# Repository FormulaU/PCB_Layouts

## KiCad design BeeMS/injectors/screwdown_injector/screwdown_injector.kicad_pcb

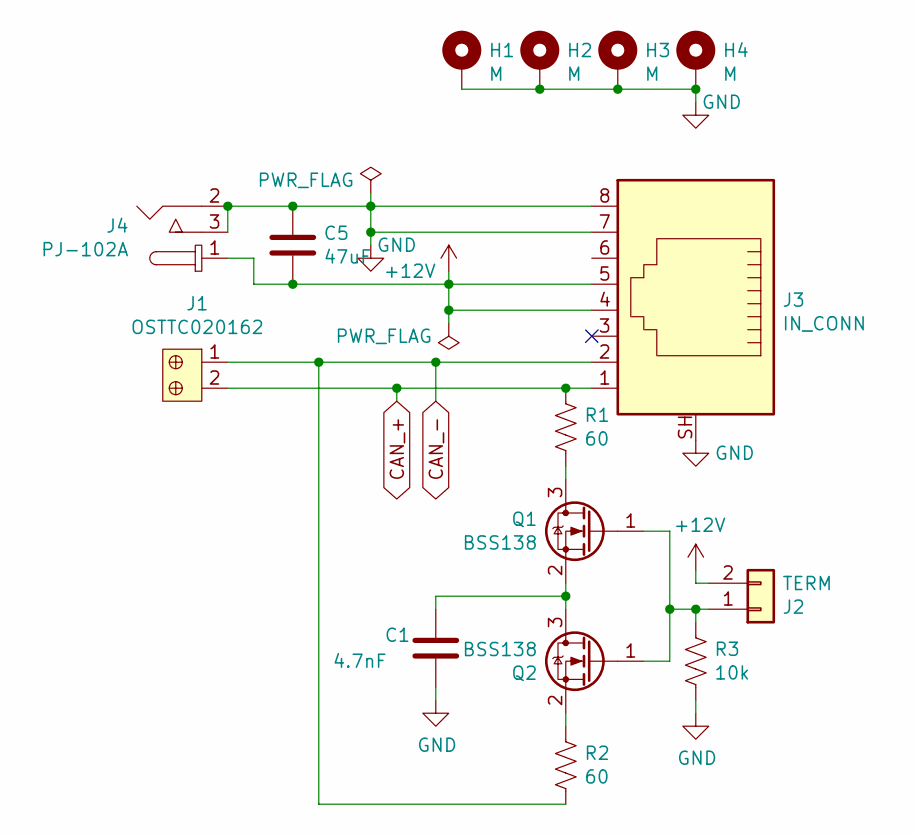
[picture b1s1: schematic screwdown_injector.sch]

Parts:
C1: 4.7nF; C_1206_3216Metric_Pad1.42x1.75mm_HandSolder; MPN 885012208079; Digi-Key_PN 732-8119-1-ND
C5: 47uF; C_1210_3225Metric_Pad1.42x2.65mm_HandSolder; MPN RM32EC81C476KE15L; Digi-Key_PN 490-10531-1-ND
H1, H2, H3, H4: M; MountingHole_2.2mm_M2_DIN965_Pad
J1: OSTTC020162; Term_Block_1x2_P5mm; MPN OSTTC020162; Digi-Key_PN ED2600-ND
J2: TERM; PinHeader_1x02_P2.54mm_Vertical
J3: IN_CONN; RJ45_Amphenol_RJHSE5380; MPN RJHSE-5380; Digi-Key_PN RJHSE-5380-ND
J4: PJ-102A; Barrel_Jack_5.5mmODx2.1mmID_PJ-102A; MPN PJ-102A; Digi-Key_PN CP-102A-ND
Q1, Q2: BSS138; SOT-23; MPN BSS138CT; Digi-Key_PN BSS138CT-ND
R1, R2: 60; R_2512_6332Metric_Pad1.52x3.35mm_HandSolder; MPN ERJ-P08J750V; Digi-Key_PN P75ALCT-ND
R3: 10k; R_1206_3216Metric; MPN RC1206JR-0710KL; Digi-Key_PN 311-10KERCT-ND

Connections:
+12V: C5.2, J2.2, J3.4, J3.5, J4.1
CAN_+: J1.2, J3.1, R1.1
CAN_-: J1.1, J3.2, R2.2
GND: C1.2, C5.1, H1.1, H2.1, H3.1, H4.1, J3.7, J3.8, J3.SH, J4.2, J4.3, R3.2
unnamed: C1.1, Q1.2 (S), Q2.3 (D)
unnamed: J2.1, Q1.1 (G), Q2.1 (G), R3.1
unnamed: Q1.3 (D), R1.2
unnamed: Q2.2 (S), R2.1

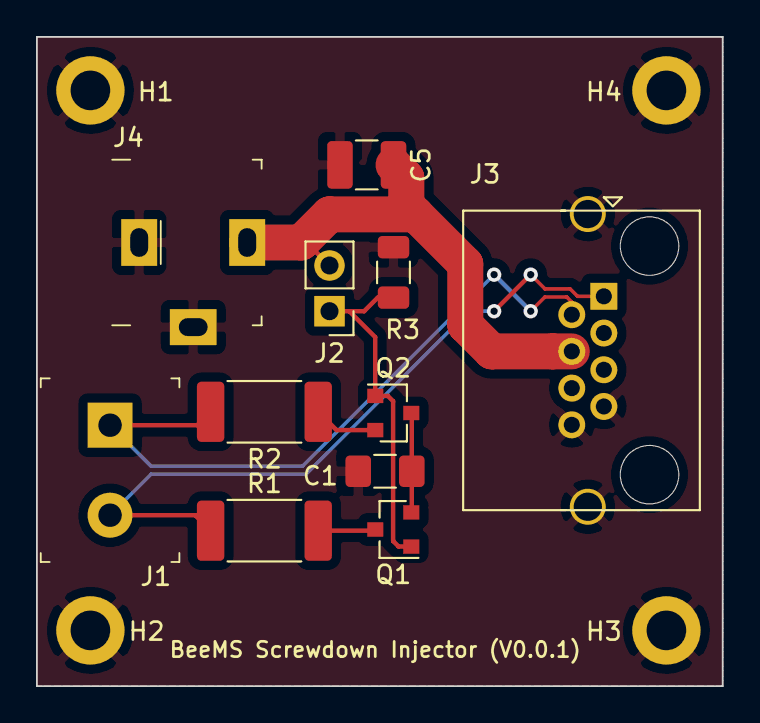
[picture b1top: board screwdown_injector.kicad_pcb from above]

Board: 2 copper layers, 38.1 x 36.1 mm, 16 parts (1 on the bottom side), 8 nets.

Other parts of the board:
svg2mod: G***; Half-U-Half-car-thresh

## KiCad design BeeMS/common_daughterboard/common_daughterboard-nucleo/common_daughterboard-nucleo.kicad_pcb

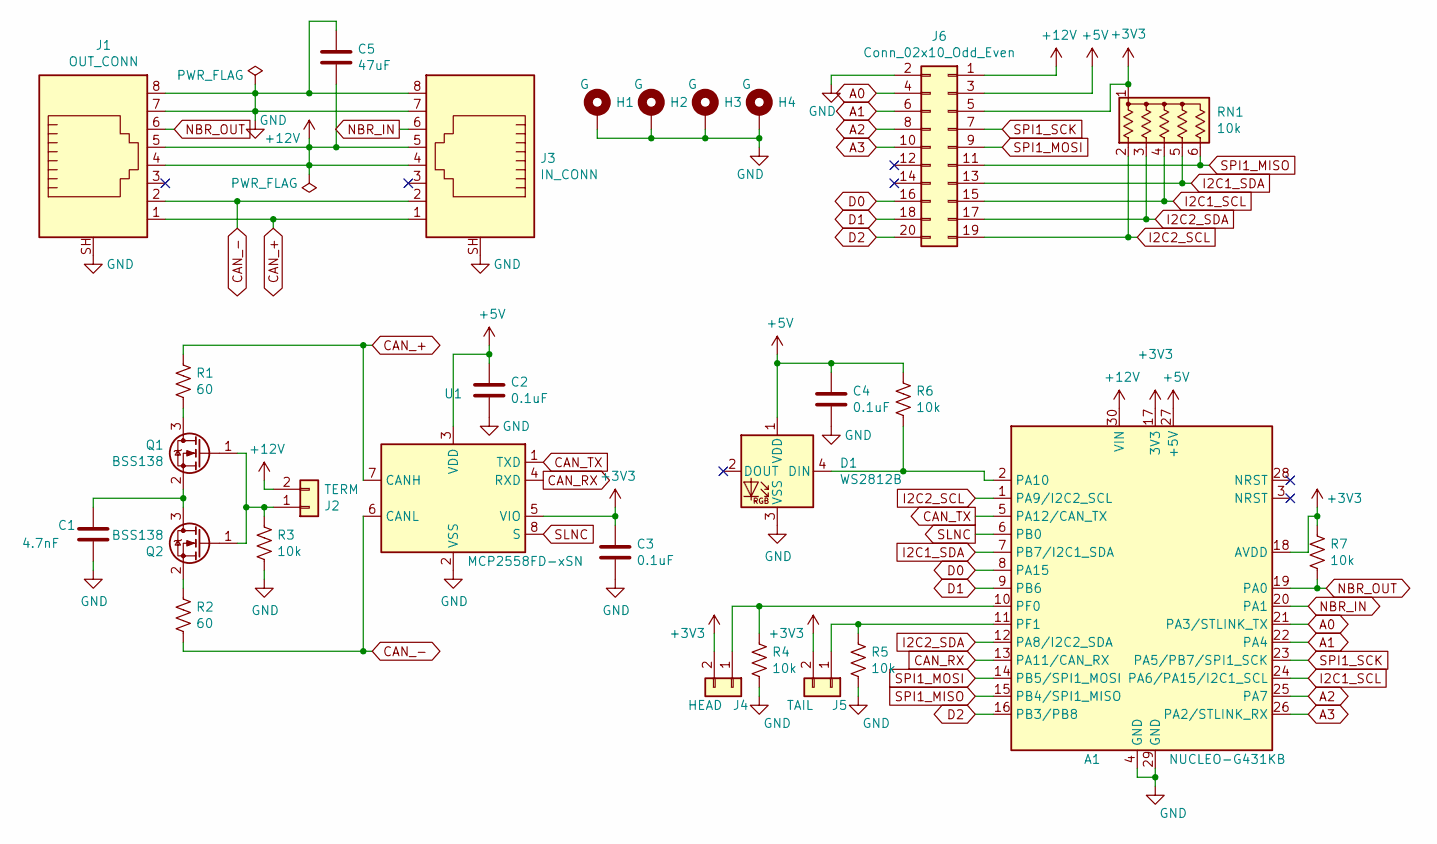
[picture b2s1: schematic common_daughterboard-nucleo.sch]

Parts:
A1: NUCLEO-G431KB; MPN NUCLEO-G431KB; Digi-Key_PN 497-19489-ND
C1: 4.7nF; C_1206_3216Metric_Pad1.42x1.75mm_HandSolder; MPN 885012208079; Digi-Key_PN 732-8119-1-ND
C2, C3, C4: 0.1uF; C_1206_3216Metric_Pad1.42x1.75mm_HandSolder; MPN 885012208087; Digi-Key_PN 732-8127-1-ND
C5: 47uF; C_1210_3225Metric_Pad1.42x2.65mm_HandSolder; MPN RM32EC81C476KE15L; Digi-Key_PN 490-10531-1-ND
D1: WS2812B; LED_WS2812B_PLCC4_5.0x5.0mm_P3.2mm; MPN COM-11821; Digi-Key_PN 1568-1800-ND
H1, H2, H3, H4: G; MountingHole_2.2mm_M2_ISO7380_Pad
J1: OUT_CONN; RJ45_Amphenol_RJHSE5380; MPN RJHSE-5380; Digi-Key_PN RJHSE-5380-ND
J2: TERM; PinHeader_1x02_P2.54mm_Vertical
J3: IN_CONN; RJ45_Amphenol_RJHSE5380; MPN RJHSE-5380; Digi-Key_PN RJHSE-5380-ND
J4: HEAD; PinHeader_1x02_P2.54mm_Vertical
J5: TAIL; PinHeader_1x02_P2.54mm_Vertical
J6: Conn_02x10_Odd_Even; PinHeader_2x10_P2.54mm_Vertical; MPN SFH11-PBPC-D10-ST-BK; Digi-Key_PN S9197-ND
Q1, Q2: BSS138; SOT-23; MPN BSS138CT; Digi-Key_PN BSS138CT-ND
R1, R2: 60; R_1206_3216Metric_Pad1.42x1.75mm_HandSolder; MPN ERJ-P08J750V; Digi-Key_PN P75ALCT-ND
R3, R4, R5, R6, R7: 10k; R_1206_3216Metric; MPN RC1206JR-0710KL; Digi-Key_PN 311-10KERCT-ND
RN1: 10k; R_Array_SIP6; MPN 4606X-AP1-103LF; Digi-Key_PN 4606X-AP1-103LFTB-ND
U1: MCP2558FD-xSN; SOIC-8_3.9x4.9mm_P1.27mm; MPN MCP2558FD-H/SN-ND; Digi-Key_PN MCP2558FD-H/SN

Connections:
+3V3: A1.17 (3V3), A1.18 (AVDD), C3.1, J4.2, J5.2, J6.5, R7.1, RN1.1 (common), U1.5 (VIO)
+5V: A1.27 (+5V), C2.1, C4.1, D1.1 (VDD), J6.3, R6.1, U1.3 (VDD)
+12V: A1.30 (VIN), C5.2, J1.4, J1.5, J2.2, J3.4, J3.5, J6.1
A0: A1.21 (PA3/STLINK_TX), J6.4
A1: A1.22 (PA4), J6.6
A2: A1.25 (PA7), J6.8
A3: A1.26 (PA2/STLINK_RX), J6.10
CAN_+: J1.1, J3.1, R1.1, U1.7 (CANH)
CAN_-: J1.2, J3.2, R2.2, U1.6 (CANL)
CAN_RX: A1.13 (PA11/CAN_RX), U1.4 (RXD)
CAN_TX: A1.5 (PA12/CAN_TX), U1.1 (TXD)
D0: A1.8 (PA15), J6.16
D1: A1.9 (PB6), J6.18
D2: A1.16 (PB3/PB8), J6.20
GND: A1.4 (GND), A1.29 (GND), C1.2, C2.2, C3.2, C4.2, C5.1, D1.3 (VSS), H1.1, H2.1, H3.1, H4.1, J1.7, J1.8, J1.SH, J3.7, J3.8, J3.SH, J6.2, R3.2, R4.2, R5.2, U1.2 (VSS)
I2C1_SCL: A1.24 (PA6/PA15/I2C1_SCL), J6.15, RN1.4 (R3)
I2C1_SDA: A1.7 (PB7/I2C1_SDA), J6.13, RN1.5 (R4)
I2C2_SCL: A1.1 (PA9/I2C2_SCL), J6.19, RN1.2 (R1)
I2C2_SDA: A1.12 (PA8/I2C2_SDA), J6.17, RN1.3 (R2)
NBR_IN: A1.20 (PA1), J3.6
NBR_OUT: A1.19 (PA0), J1.6, R7.2
unnamed: A1.2 (PA10), D1.4 (DIN), R6.2
unnamed: A1.10 (PF0), J4.1, R4.1
unnamed: A1.11 (PF1), J5.1, R5.1
unnamed: C1.1, Q1.2 (S), Q2.3 (D)
unnamed: J2.1, Q1.1 (G), Q2.1 (G), R3.1
unnamed: Q1.3 (D), R1.2
unnamed: Q2.2 (S), R2.1
SLNC: A1.6 (PB0), U1.8 (S)
SPI1_MISO: A1.15 (PB4/SPI1_MISO), J6.11, RN1.6 (R5)
SPI1_MOSI: A1.14 (PB5/SPI1_MOSI), J6.9
SPI1_SCK: A1.23 (PA5/PB7/SPI1_SCK), J6.7

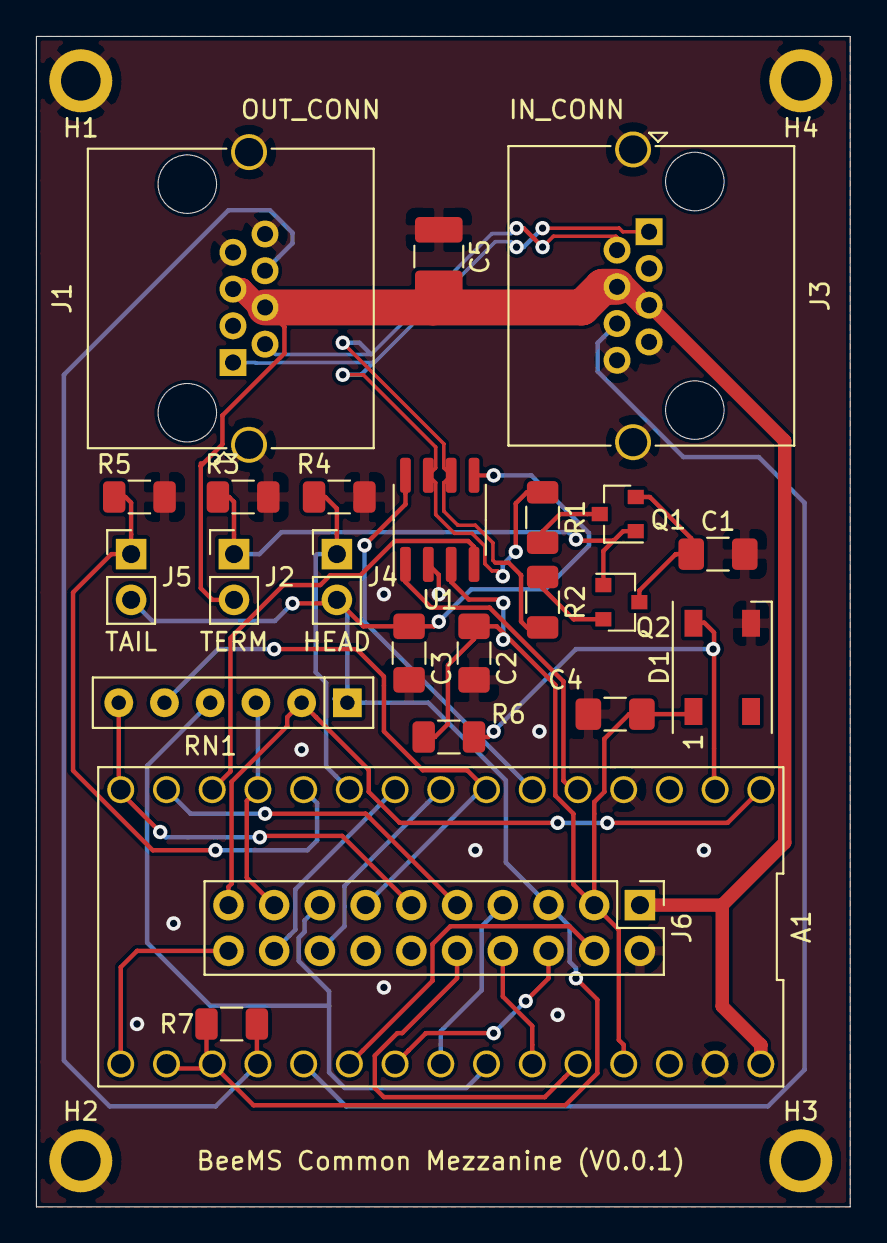
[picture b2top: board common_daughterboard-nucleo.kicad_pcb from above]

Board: 2 copper layers, 45.2 x 65.0 mm, 29 parts (1 on the bottom side), 32 nets.

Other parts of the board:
svg2mod: G***; Half-U-Half-car-thresh

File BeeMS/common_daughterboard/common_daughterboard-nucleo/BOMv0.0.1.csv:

"Id";"Designator";"Package";"Quantity";"Designation";"Supplier and ref";
1;"svg2mod";"Half-U-Half-car-thresh";1;"G***";;;
2;"C5";"C_1210_3225Metric_Pad1.42x2.65mm_HandSolder";1;"47uF";;;
3;"A1";"NUCLEO-G431KB";1;"NUCLEO-G431KB";;;
4;"J3";"RJ45_Amphenol_RJHSE5380";1;"IN_CONN";;;
5;"H4";"MountingHole_2.2mm_M2_ISO7380_Pad";1;"TR";;;
6;"H3";"MountingHole_2.2mm_M2_ISO7380_Pad";1;"BR";;;
7;"H2";"MountingHole_2.2mm_M2_ISO7380_Pad";1;"BL";;;
8;"H1";"MountingHole_2.2mm_M2_ISO7380_Pad";1;"TL";;;
9;"J6";"PinHeader_2x10_P2.54mm_Vertical";1;"Conn_02x10_Odd_Even";;;
10;"U1";"SOIC-8_3.9x4.9mm_P1.27mm";1;"MCP2558FD-xSN";;;
11;"RN1";"R_Array_SIP6";1;"10k";;;
12;"R7,R6,R5,R4,R3";"R_1206_3216Metric";5;"10k";;;
13;"R2,R1";"R_1206_3216Metric";2;"60";;;
14;"Q2,Q1";"SOT-23";2;"BSS138";;;
15;"J5";"PinHeader_1x02_P2.54mm_Vertical";1;"TAIL";;;
16;"J4";"PinHeader_1x02_P2.54mm_Vertical";1;"HEAD";;;
17;"J2";"PinHeader_1x02_P2.54mm_Vertical";1;"TERM";;;
18;"J1";"RJ45_Amphenol_RJHSE5380";1;"OUT_CONN";;;
19;"D1";"LED_Inolux_IN-PI554FCH_PLCC4_5.0x5.0mm_P3.2mm";1;"Inolux_IN-PI554FCH";;;
20;"C4";"C_1206_3216Metric_Pad1.42x1.75mm_HandSolder";1;"0.1uF";;;
21;"C3,C2";"C_1206_3216Metric_Pad1.42x1.75mm_HandSolder";2;".1uF";;;
22;"C1";"C_1206_3216Metric_Pad1.42x1.75mm_HandSolder";1;"4700pF";;;

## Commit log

2018-01-20 Teensy Baseboard Starting Point
    Read the title ya dingus
2018-01-21 Added Arduino Pro Mini 328 files, SparkFun CAM and design rules, and the Gerber files I used for the first run of the Arduino Pro Minis.
2018-01-28 Some cleanup, added Arduino Pro Mini as a placeholder for the data collectors
2018-01-29 Made 328_data_collector project, defined mezzanine connection.
2018-02-08 More work on 328 schematic. Culled regulator. Left decoupling caps, pretty sure they're overkill though. Consult Brandon and Kirby.
2018-02-25 Updated submodule URL
2018-03-04 Added brandon's circuits
2018-03-06 Brandon
    Brandon
2018-03-16 Teensy
    Teensy fixes
2018-03-16 PCB Designs
    Rev C
2019-01-11 Re-arranged folders, built segment diagram
2019-05-16 Accumulator schematic first pass
2019-05-16 Brandon update.
2020-01-14 New Eagle version
    Also patched attributes to treat schematics as binaries rather than
    text, so we don't show them in diffs.
2020-02-06 BeeMS Common Mezzanine V1 almost done
    Committing just in case the autorouter lights my layout on fire and
    pushes it down the stairs.
2020-02-15 BeeMS Common Daughterboard V0.0.1
2020-02-27 Added BOM for the nucleo common daughterboard
2020-02-27 Screwdown injector V0.0.1
2020-03-19 Added U of U Logo
2021-11-13 Files from Virtual Machine
